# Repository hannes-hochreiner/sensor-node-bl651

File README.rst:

Sensor Node BL651
~~~~~~~~~~~~~~~~~

The goal of this project is to create a simple sensor node based on the BL651 module running on a single AAA battery.

.. image:: pictures/V1_1_0_assembled.jpg

Safety Measures
===============

Reverse polarity protection
--------------------------

Reverse polarity protection is provided by a P-channel MOSFET connecting the drain to the positive terminal of the battery, the gate to ground, and the source to positive terminal of the load.

Over current protection
-----------------------

Over current protection is provided by the DC-DC-converter.
The short circuit current is max 150 mA @ about 2 V (1/3 W).

Under voltage protection
------------------------

Since the idea is to use the system with NiMH batteries, care has to be taken to not discharge them below 1.1 V.
Under voltage protection will be provided by the MCU by actively measuring the battery voltage and going into sleep mode once the threshold is reached.
This method comes with a higher risk, as the MCU has to actively measure the voltage and react to under voltage conditions.

Design
======

ADC
---

The basic setup for measuring the battery voltage is a voltage divider with R1 between V_bat and the ADC pin and R2 between the ADC pin and ground.
In parallel with R2, a capacitor (C_ext) is used to avoid big influences of the sample capacitor filling up.

For the design of the voltage measurement, a `blog post by Nordic <https://devzone.nordicsemi.com/nordic/nordic-blog/b/blog/posts/measuring-lithium-battery-voltage-with-nrf52>`_ was used as guidance.
The sample frequency (f_sample) was taken as 1/30 Hz, which should leave enough buffer for a measurement every minute.
Using the sampling frequency and the capacitance of the sample capacitor (C_sample = 2.5 pF), the effective impedance of the ADC input pin (R_input) can be calculated.

.. code-block::

    R_input = 1 / (f_sample * C_sample) = 1 / (1 / 30 * 2.5e-12) = 12e12 Ohm

To obtain good measurements, the R_input needs to be much larger than the resistor values of the voltage divider.
Assuming 12-bit resolution, C_ext comes out to be about 10 nF.

The expected voltage range of the batteries (NiMH) is 1.4-1.0 V.
The internal reference of the nRF52810 is 0.6 V.
Putting in a little margin 1.5 V were used for the calculation.

.. code-block::

    V_meas = V_bat * R2 / (R1 + R2)
    0.6 / 1.5 = R2 / (R1 + R2)
    0.4 = R2 / (R1 + R2)

Since a measurement frequency of 1/60 Hz was planned, it needs to be assured that the capacitor charges within that time.
Therefore, the time constant of tau_0 = R1 * C_ext was calculated.
A value of 15 MOhm for R1 and 100 nF (10 times the minimum calculated earlier) was assumed.

.. code-block::

    R1 = 15 MOhm = 1.5e7 Ohm
    C_ext = 100 nF = 1e-7 F
    tau_0 = 1.5e7 * 1e-7 = 1.5

The charging factor could then be calculated based on the above assumptions.

.. code-block::
    V_C_ext / V_bat = 1 - e^(-t / tau_0)
    0.9987 = 1 - e^(-10 / 1.5)

Hence, after 10 seconds the capacitor should be charged to more than 99%.
R2 can then be calculated to be 10 MOhm.

.. code-block::

    2/3 R1 = R2 = 10 MOhm

TPS60313DGS
-----------

The passives were used as given in the example circuit.
Since the second output is not being used, the decoupling capacitors for this output were not added.

Connectors
----------

Minimum pin length for the bottom entry connectors is 3.15 mm.

Sensors
=======

SHT4x
-----

This sensor worked fine with similar designs.
Due to the internal pull-ups of the nRF52810, no external pull-ups are required.

LSM303AGR
---------

This sensor worked fine with similar designs.
Due to the internal pull-ups of the nRF52810, no external pull-ups are required.

**Note**

The LSM303AGR is currently (June 2021) not available.
Therefore, additional footprints for additional sensors performing its functions were added.

MMC5603NJ
---------

This sensor replaces the magnetic sensor contained in the LSM303AGR.

MXC4005XC
---------

This sensor replaces the accelerometer contained in the LSM303AGR.

Programming
===========

The firmware for this device can be found in the repository `hannes-hochreiner/sensor-net-nrf52810-firmware <https://github.com/hannes-hochreiner/sensor-net-nrf52810-firmware>`_.
A suitable programming connector can be found in the repository `hannes-hochreiner/swd-adapter <https://github.com/hannes-hochreiner/swd-adapter>`_.

.. image:: pictures/V1_1_0_programming.jpg

Tests
=====

+-----------------------------+--------+--------+--------+
|                        Unit | V1.0.0 | V1.1.0 | V1.2.0 |
+=============================+========+========+========+
|                       Power |   OK   |   OK   |        |
+-----------------------------+--------+--------+--------+
| Reverse polarity protection |   OK   |   OK   |        |
+-----------------------------+--------+--------+--------+
|     Over current protection | Note 1 | Note 3 |        |
+-----------------------------+--------+--------+--------+
|    Under voltage protection |   tbt  |   OK   |        |
+-----------------------------+--------+--------+--------+
|                       SHT4x |   tbt  |   OK   |        |
+-----------------------------+--------+--------+--------+
|                   LSM303AGR |   tbt  | Note 4 |        |
+-----------------------------+--------+--------+--------+
|                   MMC5603NJ |   tbt  |   OK   |  N/A   |
+-----------------------------+--------+--------+--------+
|                   MXC4005XC |   tbt  | Note 5 |  N/A   |
+-----------------------------+--------+--------+--------+
|                  Connectors | Note 2 |   OK   |        |
+-----------------------------+--------+--------+--------+

**Note 1**

Over current protection did not work as intended as the resistance of the fuses was too high to start with.

**Note 2**

The footprints of both connectors had problems (although different ones).
It was possible to scrape the pads of the programming connector free and subsequently program the module.

**Note 3**

Over current protection is provided by the DC/DC converter, but was not tested.

**Note 4**

The LSM303AGR is not available at the moment (summer 2021).

**Note 5**

It was not possible to read the markings on the MXC4005XC.
There was a 50% chance of getting the orientation right.
The chip did not pass the smoke test.

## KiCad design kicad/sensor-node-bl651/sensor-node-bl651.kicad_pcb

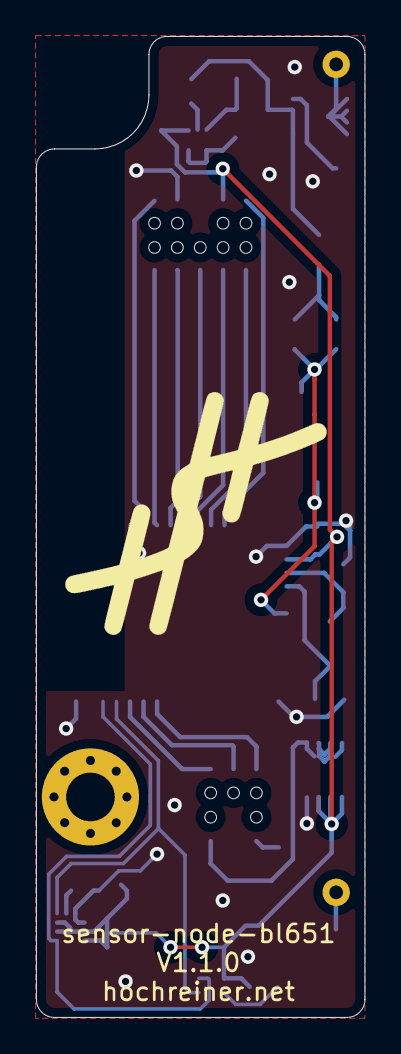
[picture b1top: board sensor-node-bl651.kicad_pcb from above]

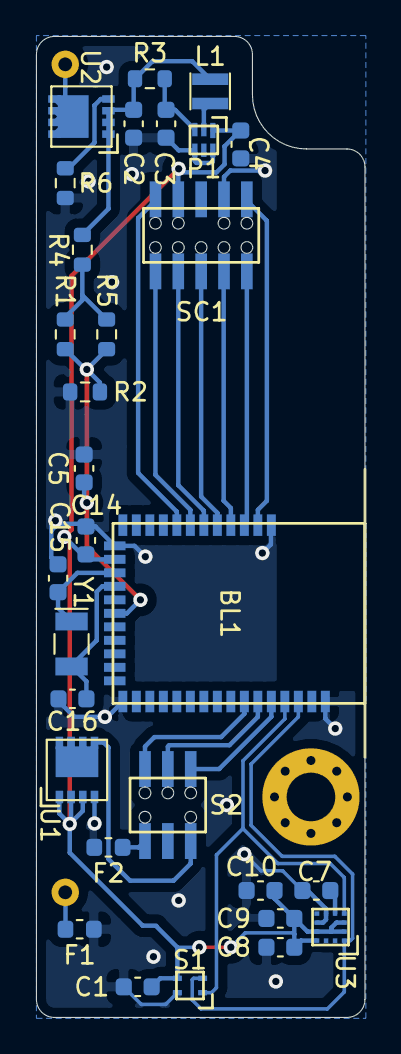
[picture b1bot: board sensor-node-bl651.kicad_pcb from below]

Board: 2 copper layers, 18.2 x 54.5 mm, 34 parts (30 on the bottom side), 27 nets.

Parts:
B1: 1551J
BL1: BL651
BT1: 0V7-4V5; AAA_179_180
C1: 0.1µF, 10V, 0603; C_0603_1608Metric
C2, C4, C10: 10µF 0603; C_0603_1608Metric
C3, C8, C9: 0.1µF 0603; C_0603_1608Metric
C5, C14: 0.1µF 0603 16V; C_0603_1608Metric
C7: 220nF 0603; C_0603_1608Metric
C15, C16: 9pF; C_0603_1608Metric
F1, F2: Fuse; Fuse_0603_1608Metric
H1: MountingHole; MountingHole_2.7mm_M2.5_Pad_Via
L1: 4.7µH; L_Taiyo-Yuden_NR-20xx
L2: logo
P1: TPS61098x
R1, R2, R4, R5: 10M 0.5% 0603 1/10W; R_0603_1608Metric
R3: 400 0603; R_0603_1608Metric
R6: 100k 0603; R_0603_1608Metric
S1: SHT4x
S2: swd_connector_keyed; SWD_BD050-06-A-0-0500-L-D
SC1: sensor_connector_keyed; Sensor-Connector_BD050-10-A-0-0500-L-D
U1, U2: DMP2008UFG-7
U3: LSM303AGR
Y1: 32.768 kHz; Crystal_SMD_MicroCrystal_CC7V-T1A-2Pin_3.2x1.5mm

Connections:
/mcu/GPIO_1: BL1.38, SC1.1
/mcu/I2C_SCL: BL1.32, SC1.9
/mcu/I2C_SDA: BL1.33, SC1.10
/mcu/SPI_CIPO: BL1.37, SC1.2
/mcu/SPI_CLK: BL1.35, SC1.6
/mcu/SPI_COPI: BL1.36, SC1.4
/mcu/SWDCLK: BL1.6, S2.4
/mcu/SWDIO: BL1.5, S2.6
/mcu/VDD: BL1.26, C1.1, C4.1, C8.1, C9.1, C10.1, C14.1, P1.1, S1.3, SC1.7, U1.1, U1.2, U1.3, U3.2, U3.3, U3.9, U3.10
/mcu/V_BAT: C2.1, L1.1, R3.1, R4.2, U2.1, U2.2, U2.3
/mcu/V_sen: BL1.22, C5.2, R1.1, R2.2, R5.1
/mcu/~RESET: BL1.7, S2.2
/mcu/~SPI_CS: BL1.34, SC1.8
/sensors/SCL: BL1.3, S1.2, U3.1
/sensors/SDA: BL1.4, S1.1, U3.4
GND: BL1.1, BL1.16, BL1.27, BL1.39, C1.2, C2.2, C3.2, C4.2, C5.1, C7.2, C8.2, C9.2, C10.2, C14.2, C15.2, C16.2, F1.1, F2.2, P1.4, P1.6, R2.1, R6.2, S1.4, SC1.3, U1.4, U3.6, U3.8
unnamed: BL1.24, C16.1, Y1.2
unnamed: BL1.25, C15.1, Y1.1
unnamed: BT1.1, U2.5, U2.6, U2.7, U2.8
unnamed: BT1.2, F1.2
unnamed: C3.1, P1.3, R3.2
unnamed: C7.1, U3.5
unnamed: F2.1, S2.1
unnamed: L1.2, P1.2
unnamed: R1.2, R4.1, R5.2
unnamed: R6.1, U2.4
unnamed: S2.5, U1.5, U1.6, U1.7, U1.8

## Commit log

2021-02-13 apply finishing touches
2021-05-30 add test results
2021-05-30 remove fuses
2021-05-30 add TPS6031x
2021-05-31 remove second measurement point
2021-05-31 update swd footprint
2021-06-01 update sensor connector
2021-06-01 update todos and add minimum pin length
2021-06-03 update sensor and swd connectors
2021-06-03 update models
2021-06-03 add more sensors
2021-06-04 add pull down on snooze line
2021-06-04 update version number
2021-06-04 clean up
2021-07-11 update README after V1.1 tests
2021-07-11 add images and programming description
2021-07-11 fix notes
2021-09-07 add pictures
2021-09-11 add fuses
2021-09-15 remove memsic sensors
